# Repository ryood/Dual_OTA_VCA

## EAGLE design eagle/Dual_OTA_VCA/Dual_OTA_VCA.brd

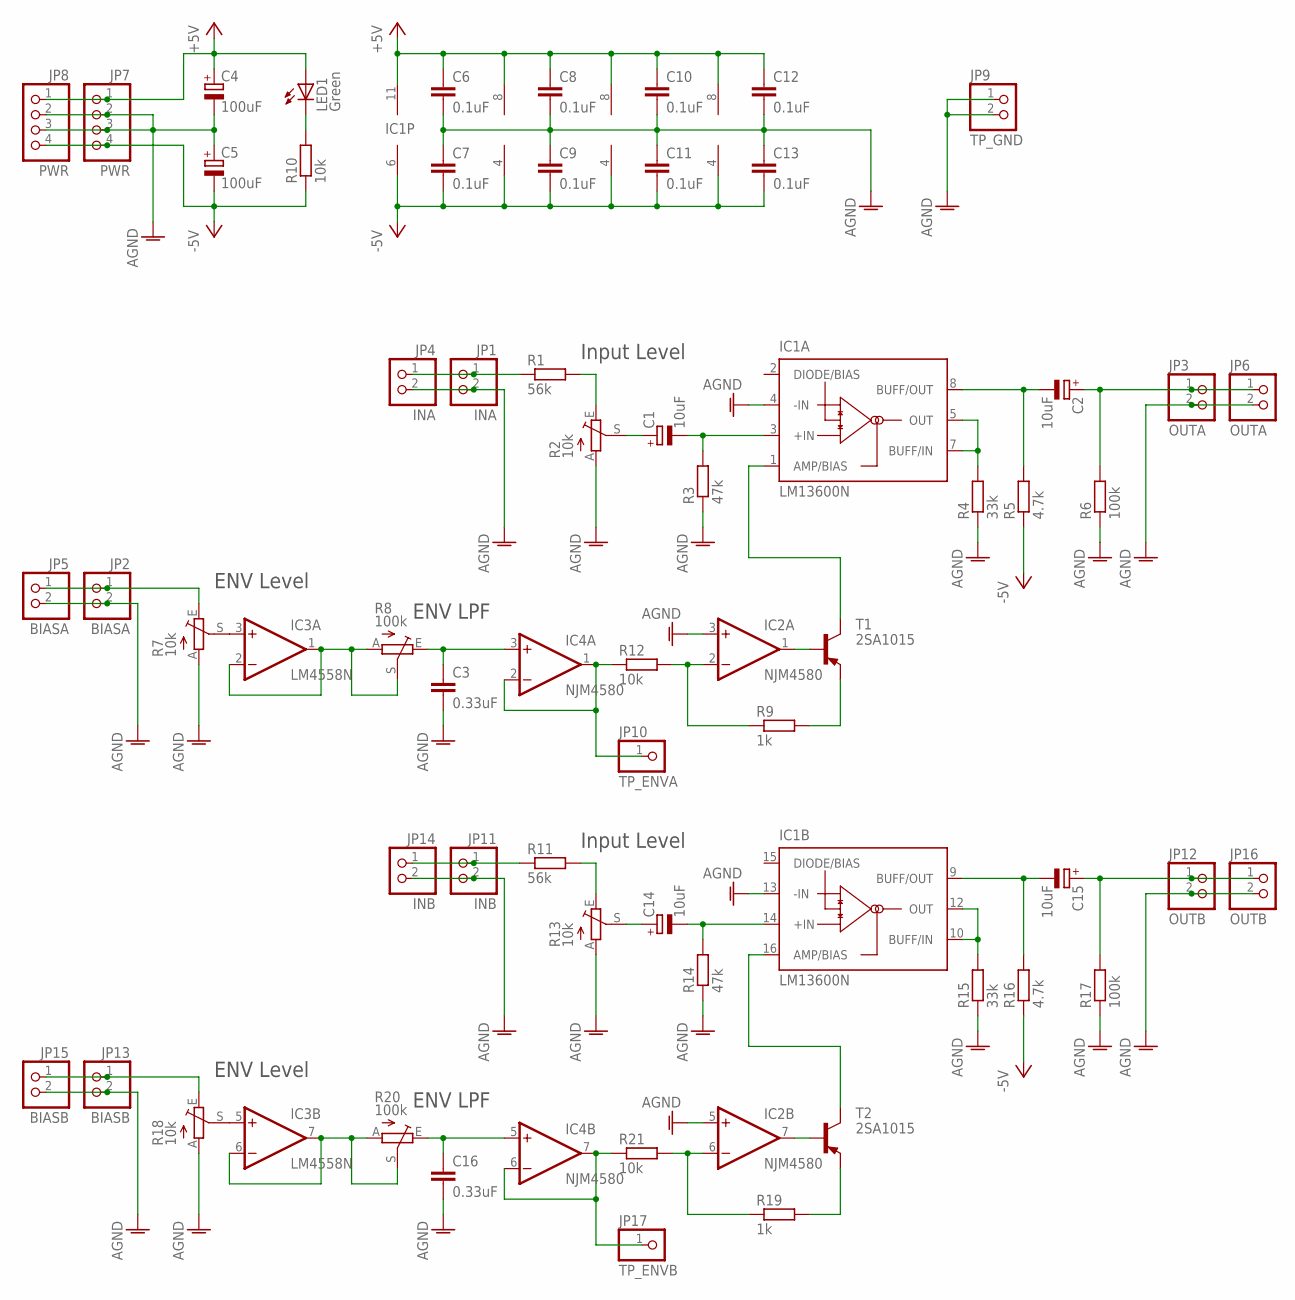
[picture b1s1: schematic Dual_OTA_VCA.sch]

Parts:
C1, C2, C14, C15: 10uF; E2,5-7
C3, C16: 0.33uF; C050-030X075
C4, C5: 100uF; E2,5-7
C6, C7: 0.1uF; C050-024X044
C8, C9, C10, C11, C12, C13: 0.1uF; C025-024X044
IC1: LM13600N; DIL16
IC2, IC4: NJM4580; DIL08
IC3: LM4558N; DIL08
JP1, JP4: INA; 1X02
JP2, JP5: BIASA; 1X02
JP3, JP6: OUTA; 1X02
JP7, JP8: PWR; 1X04
JP9: TP_GND; 1X02
JP10: TP_ENVA; 1X01
JP11, JP14: INB; 1X02
JP12, JP16: OUTB; 1X02
JP13, JP15: BIASB; 1X02
JP17: TP_ENVB; 1X01
LED1: Green; LED3MM
R1, R11: 56k; 0207/7
R2, R7, R13, R18: 10k; B25P
R3, R14: 47k; 0207/7
R4, R15: 33k; 0207/7
R5, R16: 4.7k; 0207/7
R6, R17: 100k; 0207/7
R8, R20: 100k; B25P
R9, R19: 1k; 0207/7
R10, R12, R21: 10k; 0207/7
T1, T2: 2SA1015; TO92-ECB

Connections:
+5V: C4.+, C6.1, C8.1, C10.1, C12.1, IC1.11 (V+), IC2.8 (V+), IC3.8 (V+), IC4.8 (V+), JP7.1, JP8.1, LED1.A
-5V: C5.-, C7.2, C9.2, C11.2, C13.2, IC1.6 (V-), IC2.4 (V-), IC3.4 (V-), IC4.4 (V-), JP7.4, JP8.4, R5.1, R10.1, R16.1
AGND: C3.2, C4.-, C5.+, C6.2, C7.1, C8.2, C9.1, C10.2, C11.1, C12.2, C13.1, C16.2, IC1.4 (-IN), IC1.13 (-IN), IC2.3 (+IN), IC2.5 (+IN), JP1.2, JP2.2, JP3.2, JP4.2, JP5.2, JP6.2, JP7.2, JP7.3, JP8.2, JP8.3, JP9.1, JP9.2, JP11.2, JP12.2, JP13.2, JP14.2, JP15.2, JP16.2, R2.A, R3.1, R4.1, R6.1, R7.A, R13.A, R14.1, R15.1, R17.1, R18.A
unnamed: JP1.1, JP4.1, R1.1
unnamed: R1.2, R2.E
unnamed: C1.+, R2.S
unnamed: C1.-, IC1.3 (+IN), R3.2
unnamed: IC1.5 (OUT), IC1.7 (BUFF/IN), R4.2
unnamed: C2.-, IC1.8 (BUFF/OUT), R5.2
unnamed: IC4.1 (OUT), IC4.2 (-IN), JP10.1, R12.1
unnamed: C2.+, JP3.1, JP6.1, R6.2
unnamed: IC2.2 (-IN), R9.1, R12.2
unnamed: JP2.1, JP5.1, R7.E
unnamed: R9.2, T1.E
unnamed: IC2.1 (OUT), T1.B
unnamed: IC3.5 (+IN), R18.S
unnamed: IC1.1 (AMP/BIAS), T1.C
unnamed: LED1.K (C), R10.2
unnamed: JP11.1, JP14.1, R11.1
unnamed: IC3.3 (+IN), R7.S
unnamed: IC3.1 (OUT), IC3.2 (-IN), R8.A, R8.S
unnamed: C3.1, IC4.3 (+IN), R8.E
unnamed: R11.2, R13.E
unnamed: C14.+, R13.S
unnamed: C14.-, IC1.14 (+IN), R14.2
unnamed: IC1.10 (BUFF/IN), IC1.12 (OUT), R15.2
unnamed: C15.-, IC1.9 (BUFF/OUT), R16.2
unnamed: C15.+, JP12.1, JP16.1, R17.2
unnamed: JP13.1, JP15.1, R18.E
unnamed: IC2.6 (-IN), R19.1, R21.2
unnamed: R19.2, T2.E
unnamed: IC2.7 (OUT), T2.B
unnamed: IC1.16 (AMP/BIAS), T2.C
unnamed: IC3.6 (-IN), IC3.7 (OUT), R20.A, R20.S
unnamed: C16.1, IC4.5 (+IN), R20.E
unnamed: IC4.6 (-IN), IC4.7 (OUT), JP17.1, R21.1

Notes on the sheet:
ENV LPF
ENV Level
Input Level

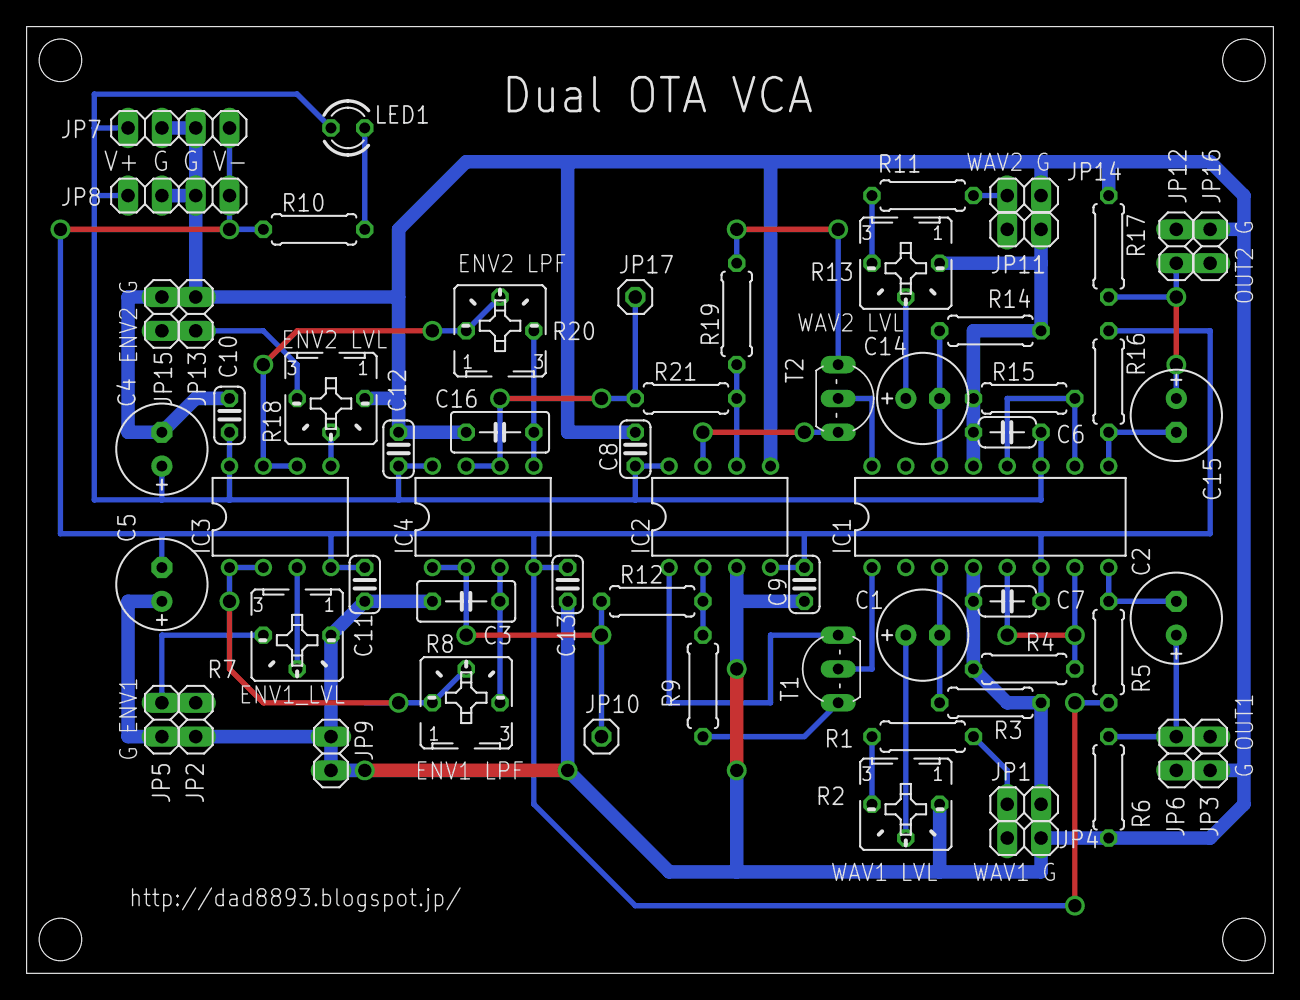
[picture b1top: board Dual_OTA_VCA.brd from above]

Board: 2 copper layers, 93.7 x 71.1 mm, 61 parts (0 on the bottom side), 36 nets.

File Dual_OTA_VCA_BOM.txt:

Partlist exported from D:/Users/gizmo/Documents/Develop/Dual_OTA_VCA/eagle/Dual_OTA_VCA/Dual_OTA_VCA.sch at 2018/04/03 14:57

Part Value    Device          Package      Description                                                                      
C1   10uF     CPOL-EUE2.5-7   E2,5-7       POLARIZED CAPACITOR, European symbol                                             
C2   10uF     CPOL-EUE2.5-7   E2,5-7       POLARIZED CAPACITOR, European symbol                                             
C3   0.33uF   C-EU050-030X075 C050-030X075 CAPACITOR, European symbol                                                       
C4   100uF    CPOL-EUE2.5-7   E2,5-7       POLARIZED CAPACITOR, European symbol                                             
C5   100uF    CPOL-EUE2.5-7   E2,5-7       POLARIZED CAPACITOR, European symbol                                             
C6   0.1uF    C-EU050-024X044 C050-024X044 CAPACITOR, European symbol                                                       
C7   0.1uF    C-EU050-024X044 C050-024X044 CAPACITOR, European symbol                                                       
C8   0.1uF    C-EU025-024X044 C025-024X044 CAPACITOR, European symbol                                                       
C9   0.1uF    C-EU025-024X044 C025-024X044 CAPACITOR, European symbol                                                       
C10  0.1uF    C-EU025-024X044 C025-024X044 CAPACITOR, European symbol                                                       
C11  0.1uF    C-EU025-024X044 C025-024X044 CAPACITOR, European symbol                                                       
C12  0.1uF    C-EU025-024X044 C025-024X044 CAPACITOR, European symbol                                                       
C13  0.1uF    C-EU025-024X044 C025-024X044 CAPACITOR, European symbol                                                       
C14  10uF     CPOL-EUE2.5-7   E2,5-7       POLARIZED CAPACITOR, European symbol                                             
C15  10uF     CPOL-EUE2.5-7   E2,5-7       POLARIZED CAPACITOR, European symbol                                             
C16  0.33uF   C-EU050-030X075 C050-030X075 CAPACITOR, European symbol                                                       
IC1  LM13600N LM13600N        DIL16        Dual Operational Transconductance Amplifiers with Linearizing Diodes and Buffers 
IC2  NJM4580  LM4558N         DIL08        OP AMP                                                                           
IC3  LM4558N  LM4558N         DIL08        OP AMP                                                                           
IC4  NJM4580  LM4558N         DIL08        OP AMP                                                                           
JP1  INA      PINHD-1X2       1X02         PIN HEADER                                                                       
JP2  BIASA    PINHD-1X2       1X02         PIN HEADER                                                                       
JP3  OUTA     PINHD-1X2       1X02         PIN HEADER                                                                       
JP4  INA      PINHD-1X2       1X02         PIN HEADER                                                                       
JP5  BIASA    PINHD-1X2       1X02         PIN HEADER                                                                       
JP6  OUTA     PINHD-1X2       1X02         PIN HEADER                                                                       
JP7  PWR      PINHD-1X4       1X04         PIN HEADER                                                                       
JP8  PWR      PINHD-1X4       1X04         PIN HEADER                                                                       
JP9  TP_GND   PINHD-1X2       1X02         PIN HEADER                                                                       
JP10 TP_ENVA  PINHD-1X1       1X01         PIN HEADER                                                                       
JP11 INB      PINHD-1X2       1X02         PIN HEADER                                                                       
JP12 OUTB     PINHD-1X2       1X02         PIN HEADER                                                                       
JP13 BIASB    PINHD-1X2       1X02         PIN HEADER                                                                       
JP14 INB      PINHD-1X2       1X02         PIN HEADER                                                                       
JP15 BIASB    PINHD-1X2       1X02         PIN HEADER                                                                       
JP16 OUTB     PINHD-1X2       1X02         PIN HEADER                                                                       
JP17 TP_ENVB  PINHD-1X1       1X01         PIN HEADER                                                                       
LED1 Green    LED3MM          LED3MM       LED                                                                              
R1   56k      R-EU_0207/7     0207/7       RESISTOR, European symbol                                                        
R2   10k      TRIM_EU-B25P    B25P         POTENTIOMETER                                                                    
R3   47k      R-EU_0207/7     0207/7       RESISTOR, European symbol                                                        
R4   33k      R-EU_0207/7     0207/7       RESISTOR, European symbol                                                        
R5   4.7k     R-EU_0207/7     0207/7       RESISTOR, European symbol                                                        
R6   100k     R-EU_0207/7     0207/7       RESISTOR, European symbol                                                        
R7   10k      TRIM_EU-B25P    B25P         POTENTIOMETER                                                                    
R8   100k     TRIM_EU-B25P    B25P         POTENTIOMETER                                                                    
R9   1k       R-EU_0207/7     0207/7       RESISTOR, European symbol                                                        
R10  10k      R-EU_0207/7     0207/7       RESISTOR, European symbol                                                        
R11  56k      R-EU_0207/7     0207/7       RESISTOR, European symbol                                                        
R12  10k      R-EU_0207/7     0207/7       RESISTOR, European symbol                                                        
R13  10k      TRIM_EU-B25P    B25P         POTENTIOMETER                                                                    
R14  47k      R-EU_0207/7     0207/7       RESISTOR, European symbol                                                        
R15  33k      R-EU_0207/7     0207/7       RESISTOR, European symbol                                                        
R16  4.7k     R-EU_0207/7     0207/7       RESISTOR, European symbol                                                        
R17  100k     R-EU_0207/7     0207/7       RESISTOR, European symbol                                                        
R18  10k      TRIM_EU-B25P    B25P         POTENTIOMETER                                                                    
R19  1k       R-EU_0207/7     0207/7       RESISTOR, European symbol                                                        
R20  100k     TRIM_EU-B25P    B25P         POTENTIOMETER                                                                    
R21  10k      R-EU_0207/7     0207/7       RESISTOR, European symbol                                                        
T1   2SA1015  -PNP-TO92-ECB   TO92-ECB     PNP Transistror                                                                  
T2   2SA1015  -PNP-TO92-ECB   TO92-ECB     PNP Transistror

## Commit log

2017-08-13 Add Bias IN Test
2017-08-13 Add spice files of V-I Convert
2017-08-13 ADD OTA_VCA with I/V Convert Test
2017-08-14 Add OTA VCAの構成
2017-08-14 Update OTA_VCAの構成
2017-08-14 Add V-I Convert Test
2017-08-14 Update OTA VCAの構成
2017-08-17 Update Schematics
2017-08-17 1ch Test
2017-08-17 begin 2ch
2017-08-19 before Parts layout
2017-08-20 Update the eagle files
2017-08-23 Board Design
2017-08-23 Update Board Design
2017-08-29 Update Board Design. Add テスト表
2018-03-25 Add: gerber files
2018-04-04 Update: テスト表(PCB)
2018-04-04 Add: Dual_OTA_VCA_BOM
2018-05-20 Add BOM
